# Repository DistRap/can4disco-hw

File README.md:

# CAN4DISCO hardware

Kicad sources for CAN4DISCO baseboard. This CAN development board accepts F4 Discovery board and
exposes CAN1 and CAN2 with two CAN transceivers.

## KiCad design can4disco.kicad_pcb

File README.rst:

CAN4DISCO hardware
==================

Kicad sources for CAN4DISCO baseboard. This CAN development board accepts F4 Discovery board and
exposes CAN1 and CAN2 with two CAN transceivers.

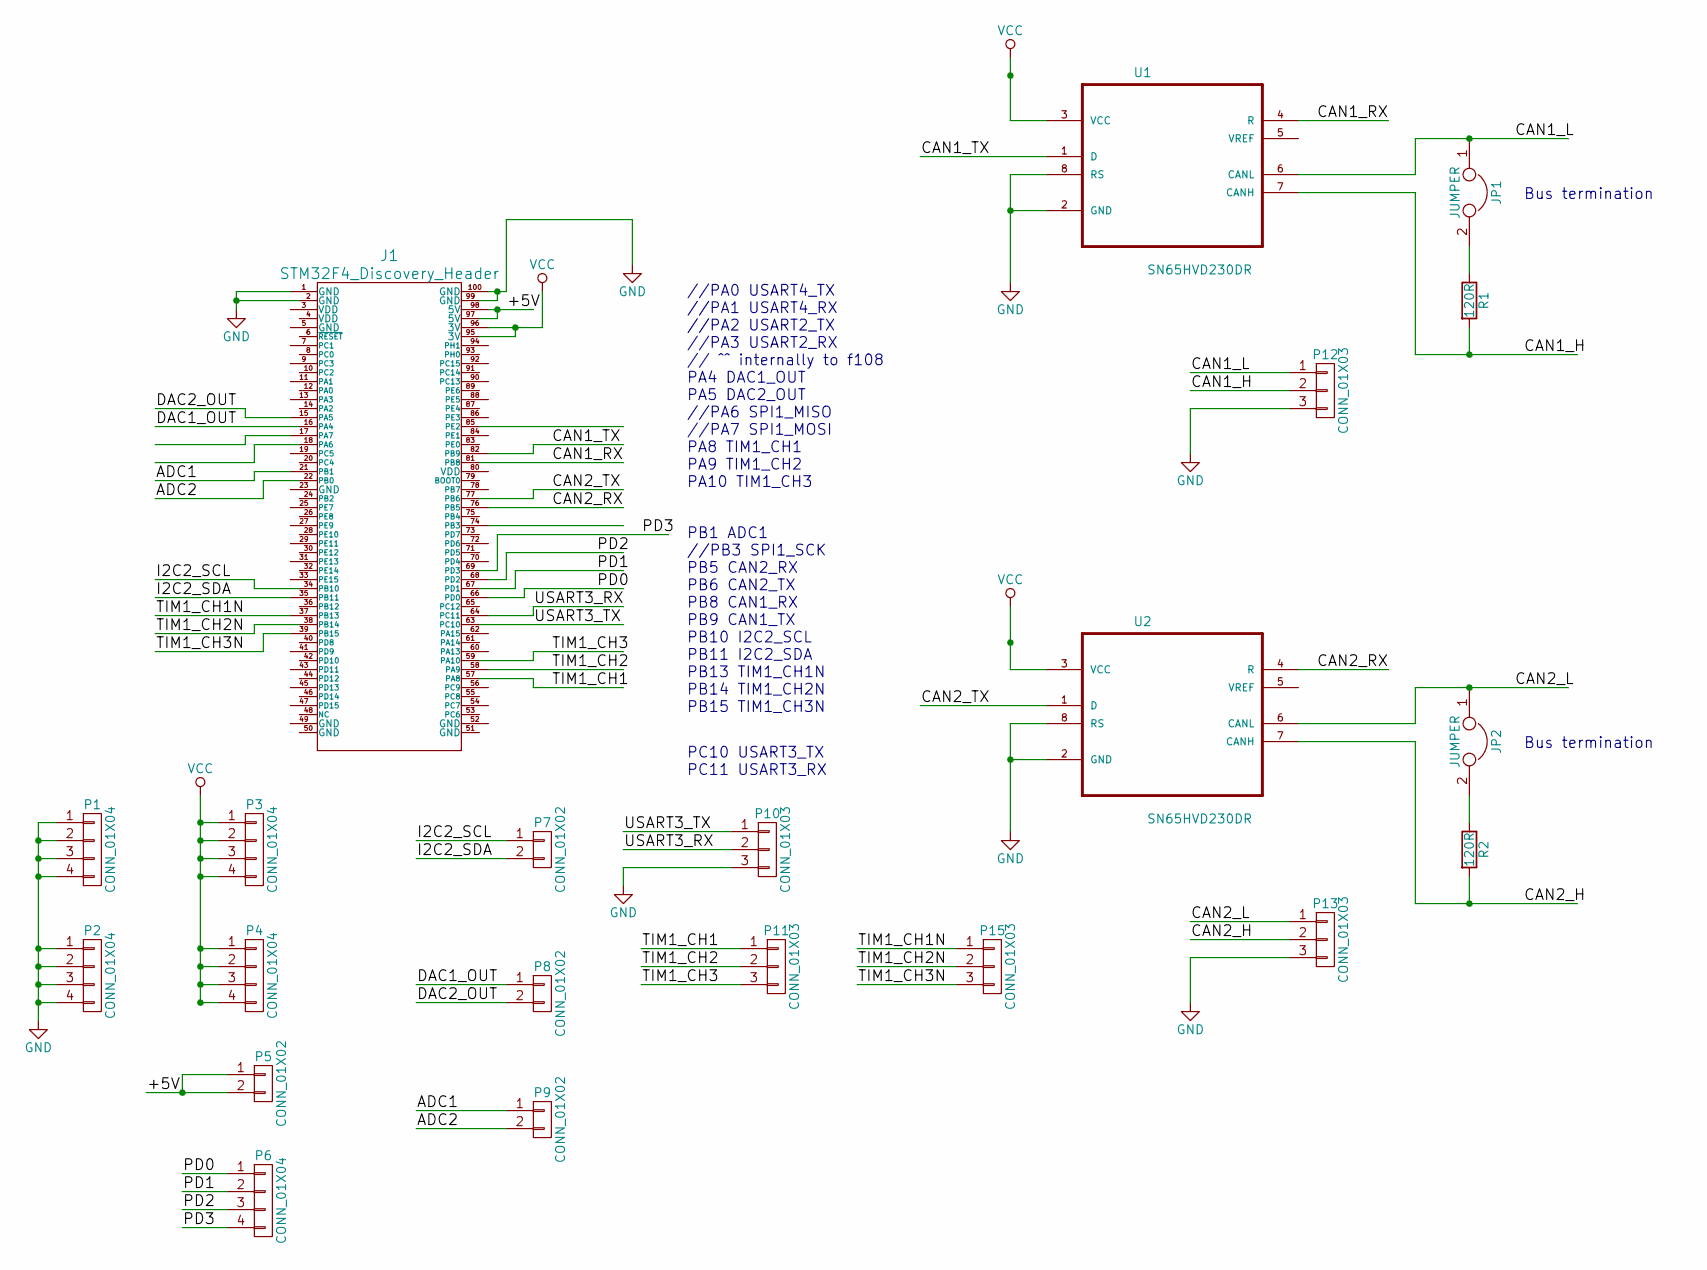
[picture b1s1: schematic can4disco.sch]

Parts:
J1: STM32F4_Discovery_Header; stm32f4_discovery_header
JP1, JP2: JUMPER; Socket_Strip_Straight_1x02
P1, P2, P3, P4, P6: CONN_01X04; Socket_Strip_Straight_1x04
P5, P7, P8, P9: CONN_01X02; Socket_Strip_Straight_1x02
P10, P11, P12, P13, P15: CONN_01X03; Socket_Strip_Straight_1x03
R1, R2: 120R; R_0805_HandSoldering
U1, U2: SN65HVD230DR; SOIC127P600X175-8N

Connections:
/+5V: J1.97 (5V), J1.98 (5V), P5.1, P5.2
/ADC1: J1.21 (PB1), P9.1
/ADC2: J1.22 (PB0), P9.2
/CAN1_H: P12.2, R1.2, U1.7 (CANH)
/CAN1_L: JP1.1, P12.1, U1.6 (CANL)
/CAN1_RX: J1.81 (PB8), U1.4 (R)
/CAN1_TX: J1.82 (PB9), U1.1 (D)
/CAN2_H: P13.2, R2.2, U2.7 (CANH)
/CAN2_L: JP2.1, P13.1, U2.6 (CANL)
/CAN2_RX: J1.76 (PB5), U2.4 (R)
/CAN2_TX: J1.77 (PB6), U2.1 (D)
/DAC1_OUT: J1.16 (PA4), P8.1
/DAC2_OUT: J1.15 (PA5), P8.2
/I2C2_SCL: J1.34 (PB10), P7.1
/I2C2_SDA: J1.35 (PB11), P7.2
/PD0: J1.66 (PD0), P6.1
/PD1: J1.67 (PD1), P6.2
/PD2: J1.68 (PD2), P6.3
/PD3: J1.69 (PD3), P6.4
/TIM1_CH1: J1.57 (PA8), P11.1
/TIM1_CH1N: J1.37 (PB13), P15.1
/TIM1_CH2: J1.58 (PA9), P11.2
/TIM1_CH2N: J1.38 (PB14), P15.2
/TIM1_CH3: J1.59 (PA10), P11.3
/TIM1_CH3N: J1.39 (PB15), P15.3
/USART3_RX: J1.64 (PC11), P10.2
/USART3_TX: J1.63 (PC10), P10.1
GND: J1.1 (GND), J1.2 (GND), J1.99 (GND), J1.100 (GND), P1.1, P1.2, P1.3, P1.4, P2.1, P2.2, P2.3, P2.4, P10.3, P12.3, P13.3, U1.2 (GND), U1.8 (RS), U2.2 (GND), U2.8 (RS)
unnamed: JP1.2, R1.1
unnamed: JP2.2, R2.1
VCC: J1.95 (3V), J1.96 (3V), P3.1, P3.2, P3.3, P3.4, P4.1, P4.2, P4.3, P4.4, U1.3 (VCC), U2.3 (VCC)

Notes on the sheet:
PB1 ADC1 //PB3 SPI1_SCK PB5 CAN2_RX PB6 CAN2_TX PB8 CAN1_RX PB9 CAN1_TX PB10 I2C2_SCL PB11 I2C2_SDA PB13 TIM1_CH1N PB14 TIM1_CH2N PB15 TIM1_CH3N
PC10 USART3_TX PC11 USART3_RX
Bus termination
//PA0 USART4_TX //PA1 USART4_RX //PA2 USART2_TX //PA3 USART2_RX // ^^ internally to f108 PA4 DAC1_OUT PA5 DAC2_OUT //PA6 SPI1_MISO //PA7 SPI1_MOSI PA8 TIM1_CH1 PA9 TIM1_CH2 PA10 TIM1_CH3

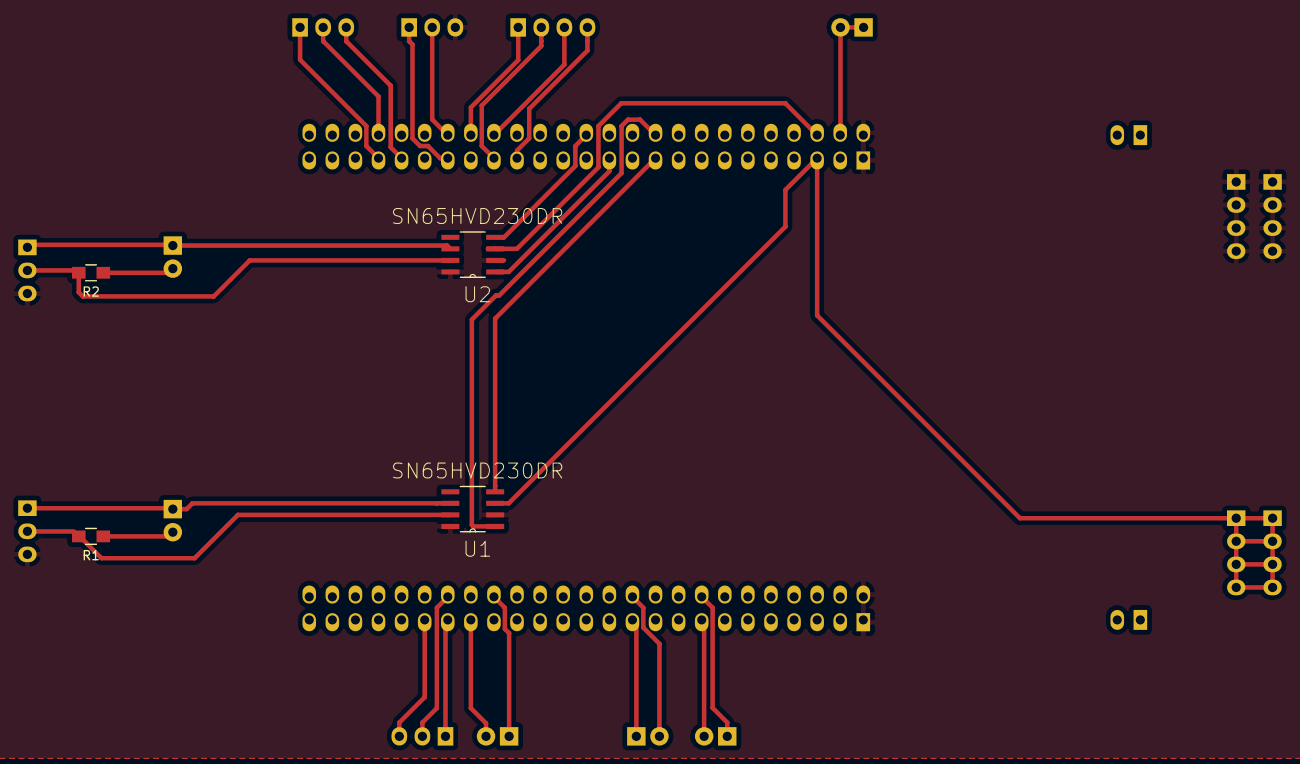
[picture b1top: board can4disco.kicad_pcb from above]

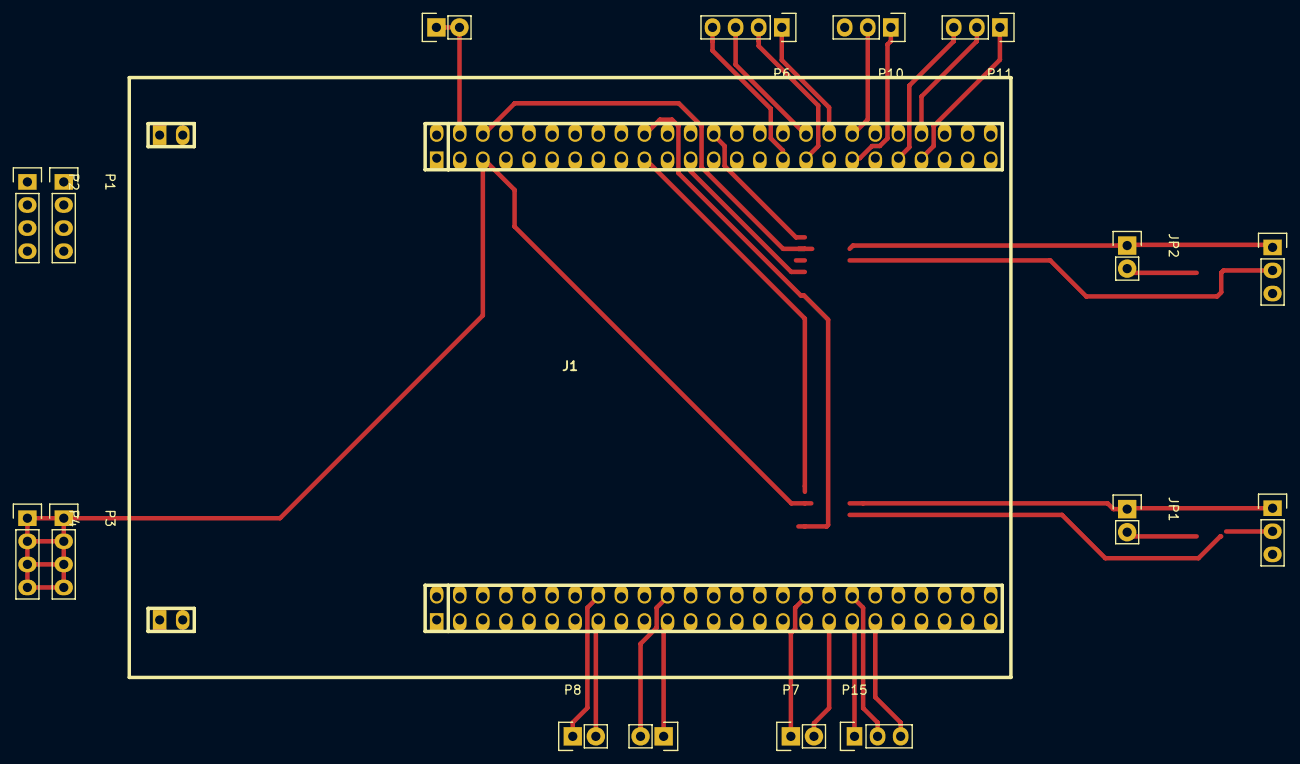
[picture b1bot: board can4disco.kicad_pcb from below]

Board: 2 copper layers, 21 parts (17 on the bottom side), 31 nets.

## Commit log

2017-03-03 initial
2017-03-03 rev 1
2017-05-10 add w_connectors from kicad-gigalib
2017-06-02 add README
2023-12-17 README.rst -> README.md
